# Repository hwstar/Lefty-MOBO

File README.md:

# Lefty-MOBO
Lefty Double Conversion Transceiver Motherboard

This is an HF Motherboard consisting of the entire signal chain from RF in to Speaker, and from Microphone to RF out.  A double conversion topology was chosen to allow the motherboard to operate on all HF bands with minimal intermodulation products close to the operating frequency.

The design uses 5 AS169-73 Skyworks RF switches,  3 Mini Circuits ADE-1 mixers, a pair 45.1 MHz matched Golledge 15 KHz BW IF filters, 6 matched 12.288 MHz crystals for the second IF SSB filter, and 3 2SC3357 low noise RF transistors in the 45.1 MHz "transverter" section. The speaker amplifier is an LM380.

This design was inspired from W7ZOI's single conversion "Lichen" Transceiver originally published in EMRFD. I use the dual JFET IF amplifer, AGC circuit, 3 transistor post-detector audio amplifier, and TX speech amplifier from that design in this design.

Please note that this is not a complete Transceiver system. The transceiver board will additionally require a 3 output VFO (My implementation uses one SI5351, and may use 2 of them in the future so that I can drive all the Mixers at 8mA) ,  external bandpass filter bank, an RF power amplifier, and a TX low pass filter bank.

Mixer 1 (U801) serves as a downconverter in RX mode, and a balanced modulator TX mode. This converts the 45.1 MHz first IF to 12.288 MHz second IF. In TX mode, the VFO provides the carrier frequency (which depends on the characteristics of the crystal filter)

Mixer 2 (U1301) serves as the product detector in RX mode, and a 12.288 MHz upconverter in TX mode.

Mixer 3 (U2201) provides downconversion from the 45.1 MHz first IF to the desired HF band.

Mixer 1, The first IF amplifier, and Mixer 2 operate in the same direction for both TX and RX, but the mixers change function depending upon whether they're being used in TX or RX. A pair of AS169-73 RF switches, some RF chokes and RF traps are used to select the TX mode, and to filter out RF from getting into the audio stages.

The 45.1 MHz first IF uses the "BITx" concept with 2SC3357 bidirectional amplifiers i.e. left-to-right, and right-to-left controlled by a pair of AS169-73 RF switches, and the P13V8_RX and P13V8_TX power rails. The 2SC3357's are biased for 40mA operation.

After Mixer3 there is a stage of TX RF amplification using a 2SC3357 to bring up the signal level what is required for the RF power amplifier (not included on this board). This amplifier is bypassed in RX mode using a AS169-73.

All control to the Lefty Motherboard is done over I2C using an NXP PCA9554 at 7 bit address 0x38. This allows the wiring from the Motherboard to be minimal. 
The I2C interface allows control AS169-73 RF switches, PTT, Rx Audio Mute circuit, AGC on/off, and the TX tune audio oscillator. The SCL and SDA pins at the connector operate at 3.3V and are intended to be used with newer 3.3V microcontrollers available such as the STM32 "black pill".

There is an I2C EEPROM on the board to facilitate storing the TX gain values for each band, and crystal filter 6dB points and bandwidth, and a DAC which is used to control the 12.288 MHz IF amplifier's gain in TX to help flatten out the TX power across all bands. TX gain may also be set manually by removing the DAC and and installing a 20K pot at R918. 

The PCB design was done with KiCAD 5.0. The BOM files are in .csv format and are included in the top level directory. There is a combined BOM, separate top and bottom SMT BOM's, and a PTH BOM.

The gerber files are in the directory TRX_MB_C2_X1

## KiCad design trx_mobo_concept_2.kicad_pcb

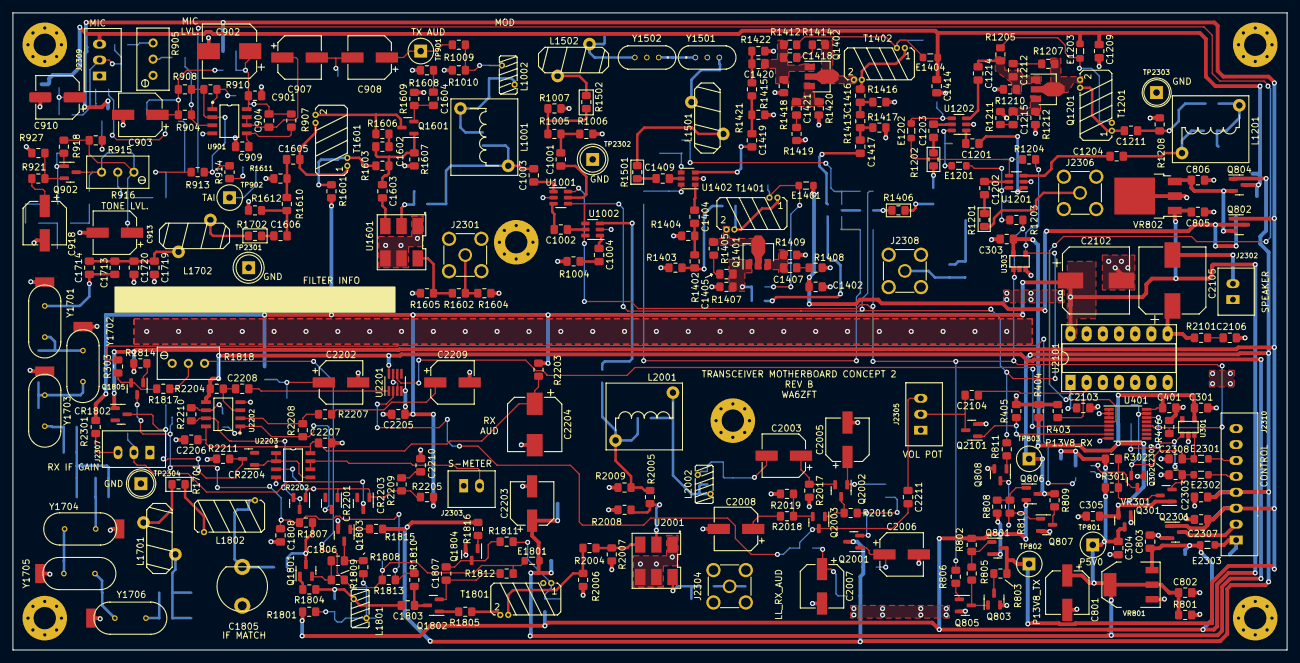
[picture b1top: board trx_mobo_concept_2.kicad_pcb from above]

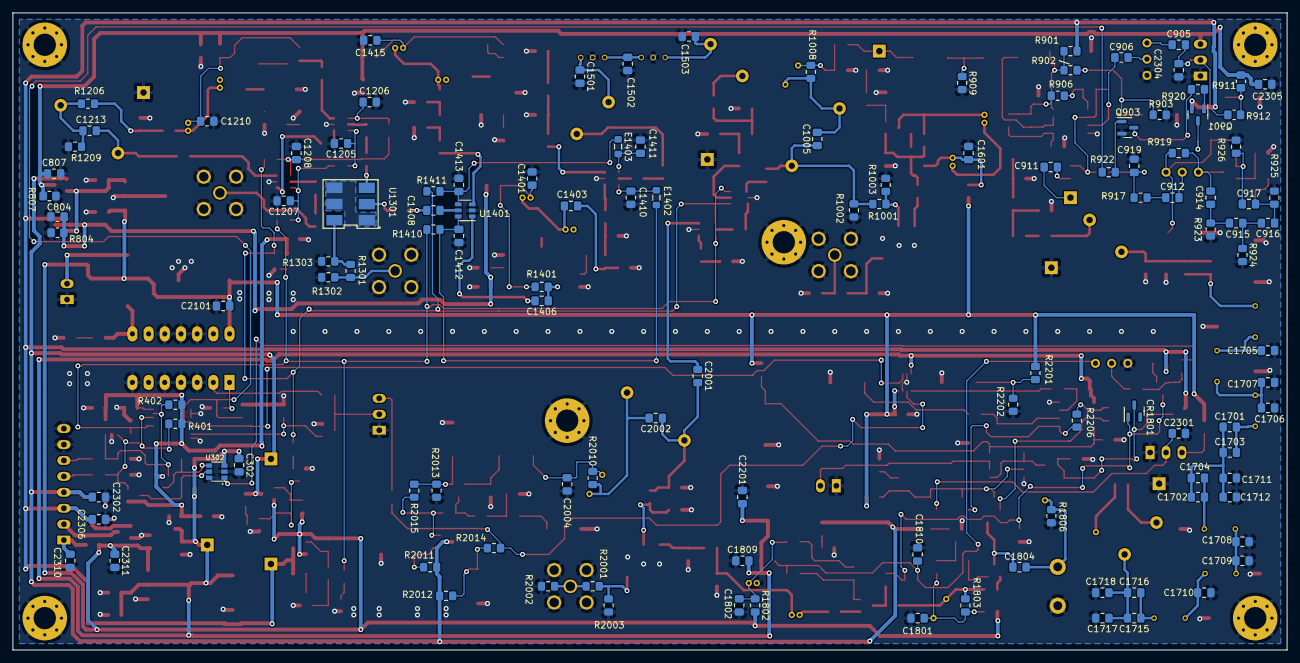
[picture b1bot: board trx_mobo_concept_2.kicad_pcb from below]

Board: 2 copper layers, 200.0 x 100.0 mm, 422 parts (119 on the bottom side), 226 nets.

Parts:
C301, C302, C303, C401, C802, C804, C807, C901, C905, C906, C911, C912, C1004, C1201, C1202, C1203, C1204, C1209, C1210, C1211, C1212, C1214, C1215, C1601, C1602, C1603, C1604, C1605, C1606, C1801, C1802, C1806, C1807, C1808, C1809, C1810, C2004, C2101, C2106, C2201, C2205, C2206, C2207, C2208, C2301, C2302, C2305, C2306, C2310, C2311: 0.1u; C_0805_2012Metric_Pad1.18x1.45mm_HandSolder
C304, C2210: 1u; C_0805_2012Metric_Pad1.18x1.45mm_HandSolder
C305, C2303, C2307: 10u; C_0805_2012Metric_Pad1.18x1.45mm_HandSolder
C801, C903, C907, C908, C910, C913, C918, C2003, C2005, C2006, C2007, C2008, C2202, C2203, C2209: 22u; CP_Elec_6.3x5.7
C803, C805, C806, C2103, C2104, C2211: 4.7u; C_0805_2012Metric_Pad1.18x1.45mm_HandSolder
C902, C2204: 100u; CP_Elec_8x10
C904, C919, C1001, C1002, C1401, C1402, C1403, C1404, C1405, C1406, C1407, C1408, C1409, C1414, C1415, C1416, C1417, C1418, C1419, C1420, C1421, C1803, C1804: 0.01u; C_0805_2012Metric_Pad1.18x1.45mm_HandSolder
C909, C914, C915, C916, C917: 0.0027u; C_0805_2012Metric_Pad1.18x1.45mm_HandSolder
C1003, C1205, C1206, C1207, C1208, C1410, C1411, C1412, C1413, C2001, C2304: 1000p; C_0805_2012Metric_Pad1.18x1.45mm_HandSolder
C1005, C1213, C1706, C1712, C1713, C1717, C1719, C2002: 150p; C_0805_2012Metric_Pad1.18x1.45mm_HandSolder
C1501, C1503: 16p; C_0805_2012Metric_Pad1.18x1.45mm_HandSolder
C1502: 13p; C_0805_2012Metric_Pad1.18x1.45mm_HandSolder
C1701, C1702: 430p; C_0805_2012Metric_Pad1.18x1.45mm_HandSolder
C1703, C1704: 15p; C_0805_2012Metric_Pad1.18x1.45mm_HandSolder
C1705, C1710: 120p; C_0805_2012Metric_Pad1.18x1.45mm_HandSolder
C1707, C1708, C1714, C1715: 10p; C_0805_2012Metric_Pad1.18x1.45mm_HandSolder
C1709, C1716: 150P; C_0805_2012Metric_Pad1.18x1.45mm_HandSolder
C1711: 18p; C_0805_2012Metric_Pad1.18x1.45mm_HandSolder
C1718, C1720: 20p; C_0805_2012Metric_Pad1.18x1.45mm_HandSolder
C1805: 60p; Cap_Trimmer_THT_6mm_plastic
C2102, C2105: 470u; CP_Elec_10x10
C2308, C2309: 100p; C_0805_2012Metric_Pad1.18x1.45mm_HandSolder
CR1801, CR1802, CR2201, CR2202, CR2203, CR2204: BAT54; SOT23-3-SAR-V2
E1201, E1202, E1203, E1401, E1402, E1403, E1404, E1801, E2301, E2302, E2303: FB0805; L_0805_2012Metric_Pad1.05x1.20mm_HandSolder
J2301, J2304, J2306, J2308: CONN_SMA_VERT; SMA_Kinghelm_KHSMA-KE8-G_Vertical
J2302, J2303: CONN2; JST_B2B_XH_A
J2305, J2307, J2309: CONN3; JST_B3B_XH_A
J2310: CONN8; JST_B8B_XH_A
L1001, L1201, L2001: 81nH; AIR_CORE_9MMX6.3MM
L1002, L1801: 27uH; IND_Handwound_FT23
L1501, L1502: 0.563uH; TOROID_T37_VERT
L1701, L1702: 0.97uH; TOROID_T37_VERT
L1802: 4.13uH; IND_Handwound_FT37
L2002: 15uH; IND_Handwound_FT23
MH2301, MH2302, MH2303, MH2304, MH2305, MH2306: MountingHole_Pad; MountingHole_3.5mm_Pad_Via
Q301, Q302, Q803, Q807, Q1805, Q2101, Q2301: BSS138; SOT-23
Q801, Q802, Q804, Q806: SI2369; SOT-23
Q805, Q808, Q902, Q903, Q1601, Q1803, Q1804, Q2001, Q2002, Q2003: MMBT3904; SOT23-3-SAR-V2
Q901: MMBT3906; SOT23-3-SAR-V2
Q1201, Q1401, Q1402: 2SC3357; SOT-89-3
Q1801, Q1802: MMBFJ310; SOT23-3-SAR-V2
R301, R302, R401, R402, R802, R806, R808, R811, R902, R903, R904, R906, R907, R927, R1815, R1816, R2015, R2201, R2202, R2206, R2207, R2210, R2211, R2301: 10K; R_0805_2012Metric_Pad1.15x1.40mm_HandSolder
R303, R805, R810, R901, R921, R2018, R2203: 100; R_0805_2012Metric_Pad1.15x1.40mm_HandSolder
R403, R404, R405, R406, R915, R1009, R2012, R2014, R2209: 1K; R_0805_2012Metric_Pad1.15x1.40mm_HandSolder
R801: 470; R_0805_2012Metric_Pad1.15x1.40mm_HandSolder
R803, R809, R1211, R1601: 10; R_0805_2012Metric_Pad1.15x1.40mm_HandSolder
R804, R807: 10K; R_0805_2012Metric_Pad1.20x1.40mm_HandSolder
R905, R916, R1818: 20K; Potentiometer_Bourns_3296W_Vertical_Screw_SS
R908: 680; R_0805_2012Metric_Pad1.15x1.40mm_HandSolder
R909: 2K; R_0805_2012Metric_Pad1.15x1.40mm_HandSolder
R910, R1813, R1814: 270K; R_0805_2012Metric_Pad1.15x1.40mm_HandSolder
R911: 100; R_0805_2012Metric_Pad1.20x1.40mm_HandSolder
R912: 6.8K; R_0805_2012Metric_Pad1.20x1.40mm_HandSolder
R913, R2204, R2208: 100K; R_0805_2012Metric_Pad1.15x1.40mm_HandSolder
R914: 100K; R_0805_2012Metric_Pad1.20x1.40mm_HandSolder
R917, R920, R922, R923, R924, R925, R2011: 47K; R_0805_2012Metric_Pad1.15x1.40mm_HandSolder
R918: 75K; R_0805_2012Metric_Pad1.15x1.40mm_HandSolder
R919: 22K; R_0805_2012Metric_Pad1.15x1.40mm_HandSolder
R926, R1807, R1808, R1810, R1811: 39K; R_0805_2012Metric_Pad1.15x1.40mm_HandSolder
R1001, R1005, R1201, R1202, R1406, R1501, R1502, R1701, R1702, R1817: 0; R_0805_2012Metric_Pad1.15x1.40mm_HandSolder
R1002, R1003, R1006, R1007: DNI; R_0805_2012Metric_Pad1.15x1.40mm_HandSolder
R1004, R1010: 51; R_0805_2012Metric_Pad1.15x1.40mm_HandSolder
R1008, R1803, R1806, R2010: 2.2K; R_0805_2012Metric_Pad1.15x1.40mm_HandSolder
R1203, R1204, R1410, R1411: 33; R_0805_2012Metric_Pad1.15x1.40mm_HandSolder
R1205, R1401, R1412: 1.1K; R_0805_2012Metric_Pad1.15x1.40mm_HandSolder
R1206, R1402, R1413, R1415, R1610, R2005: 36; R_0805_2012Metric_Pad1.15x1.40mm_HandSolder
R1207: 910; R_0805_2012Metric_Pad1.15x1.40mm_HandSolder
R1208, R1209, R1403, R1404, R1416, R1417, R1421, R1422, R1611, R1612, R2008, R2009: 150; R_0805_2012Metric_Pad1.15x1.40mm_HandSolder
R1210, R1407, R1418: 360; R_0805_2012Metric_Pad1.15x1.40mm_HandSolder
R1212, R1409, R1420: 30; R_0805_2012Metric_Pad1.15x1.40mm_HandSolder
R1301, R1602, R2001, R2004: 18; R_0805_2012Metric_Pad1.15x1.40mm_HandSolder
R1302, R1303, R1604, R1605, R2002, R2003, R2006, R2007: 300; R_0805_2012Metric_Pad1.15x1.40mm_HandSolder
R1405, R1414, R1606: 1.6K; R_0805_2012Metric_Pad1.15x1.40mm_HandSolder
R1408, R1419, R1608: 6.8; R_0805_2012Metric_Pad1.15x1.40mm_HandSolder
R1603: 8.2K; R_0805_2012Metric_Pad1.15x1.40mm_HandSolder
R1607: 1.5K; R_0805_2012Metric_Pad1.15x1.40mm_HandSolder
R1609: 120; R_0805_2012Metric_Pad1.15x1.40mm_HandSolder
R1801, R1802, R1804, R1805: 82; R_0805_2012Metric_Pad1.15x1.40mm_HandSolder
R1809, R1812: 390; R_0805_2012Metric_Pad1.15x1.40mm_HandSolder
R2013, R2017: 3.3K; R_0805_2012Metric_Pad1.15x1.40mm_HandSolder
R2016: 6.8K; R_0805_2012Metric_Pad1.15x1.40mm_HandSolder
R2019: 4.7K; R_0805_2012Metric_Pad1.15x1.40mm_HandSolder
R2101: 2.7; R_0805_2012Metric_Pad1.15x1.40mm_HandSolder
R2205: 2.2M; R_0805_2012Metric_Pad1.15x1.40mm_HandSolder
T1201, T1401, T1402, T1601: XFMR_RF_BIFILAR; XFMR_Handwound_FT37
T1801: FT37-43; XFMR_Handwound_FT37
TP801, TP802, TP803, TP901, TP902, TP2301, TP2302, TP2303, TP2304: TESTPINTPSQ025; TESTPIN
U301: 24CW640; SOT23-5-SAR
U302: MCP4725; SOT23-6-SAR
U303: 74LVC1G00; SOT23-5-SAR
U401: PCA9554APW; TSSOP-16_4.4x5mm_P0.65mm
U901, U2202, U2203: LMC6482; SOIC8N-SAR
U1001, U1002, U1201, U1202, U1401, U1402: AS169-73; SOT-23-6
U1301, U1601, U2001: ADE-1; MCL-6-SMD_7R97X5R59
U2101: LM380N; DIP-14_W7.62mm_Socket_LongPads
U2201: DG449DS-T1-E3; SOT-23-8_Handsoldering
VR301: ME6211A33M3G-N; SOT23-3-SAR-V2
VR801: NCP1117-5.0_SOT223; SOT-223-TAB-2-SAR
VR802: MC78M08CDTRKG; TO-252-3_TabPin2
Y1501, Y1502: 45.1 MHz; MCF-1.875_7.8x3.2
Y1701, Y1702, Y1703, Y1704, Y1705, Y1706: 12.288 MHz; Crystal_HC49_Vertical_With_Grounding_Pad

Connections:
/top/DIS_AGC_3V3: R404.1, U401.5 (IO1), U2201.6 (IN)
/top/ENA_TUNE_OSC_3V3: R403.1, R922.2, U401.4 (IO0)
/top/IF_GAIN_WIPER: C2301.1, CR2203.3 (C), J2307.2
/top/LO_FIRST: J2301.1, R1602.2, R1604.1
/top/LO_SECOND: J2304.1, R2001.2, R2002.1
/top/P5V0: C302.1, C304.1, C801.1, C802.1, C1809.1, C2201.1, C2203.1, E1801.1, R301.1, R302.1, R801.1, R2204.1, TP801.1 (TP), U302.3 (VDD), U2201.8, U2202.5 (+), VR301.3 (IN), VR801.2 (OUT)
/top/P13V8: C803.1, C805.1, C2101.1, C2102.1, C2205.1, C2311.1, E2303.2, Q801.2 (S), Q806.2 (S), R802.1, R808.1, R1601.2, R1801.2, R1802.2, R2201.2, R2203.2, R2205.2, R2301.1, U2101.14, U2201.4 (V+), VR801.3 (IN), VR802.1 (IN)
/top/P13V8_RX: C2302.1, C2303.1, J2310.4, Q804.1 (G), Q806.3 (D), Q2001.3 (C), R809.1, R1815.2, R1816.2, R2011.1, R2012.1, TP803.1 (TP)
/top/P13V8_TX: C2306.1, C2307.1, CR1802.1 (A), J2310.3, Q801.3 (D), Q802.1 (G), Q901.2 (E), Q2301.1 (G), R803.1, R901.2, R1814.1, TP802.1 (TP)
/top/PTT_3V3: R406.1, R806.2, R1203.2, R1410.2, U303.1, U303.2, U401.12 (IO7), U1001.6 (V2), U1002.6 (V2)
/top/PTT_3V3_N: R811.2, R1204.2, R1411.2, U303.4, U1001.4 (V1), U1002.4 (V1)
/top/RX_AUDIO_SPEAKER: C2105.2, J2302.2
/top/RX_AUDIO_TOP: C2211.1, J2305.3
/top/RX_AUDIO_WIPER: C2104.2, J2305.2, Q2101.3 (D)
/top/SCL_I2C_3V3: C2309.1, E2302.2, Q301.2 (S), R401.2, U301.1 (SCL), U401.14 (SCL)
/top/SDA_I2C_3V3: C2308.1, E2301.2, Q302.2 (S), R402.2, U301.3 (SDA), U401.15 (SDA)
/top/S_METER: J2303.2, U2203.6 (-), U2203.7
/top/TRX_RF: J2306.1, R1201.2
/top/TX_AUDIO_IN: C905.2, C2304.1, J2309.2, R912.1
/top/connectors/LO_THIRD: J2308.1, R1301.2, R1302.1
/top/connectors/P8V0_TX: C807.1, C1209.1, C1414.1, C2305.1, E1203.1, E1404.1, J2309.3, Q804.3 (D), R807.1, R911.2
/top/connectors/SCL_I2C_CONN_3V3: E2302.1, J2310.5
/top/connectors/SDA_I2C_CONN_3V3: E2301.1, J2310.6
/top/connectors/~TX: J2310.2, Q2301.3 (D)
/top/i2c/SCL_I2C_5V0: Q301.3 (D), R301.2, U302.5 (SCL)
/top/i2c/SDA_I2C_5V0: Q302.3 (D), R302.2, U302.4 (SDA)
/top/i2c/TX_IF_GAIN: Q1805.2 (S), R303.1, R1817.2
/top/radio/MUTE_RX_AUDIO: Q2101.1 (G), R405.1, U401.7 (IO3)
/top/radio/ifagc/AGC_IN: CR1801.3 (C), CR1802.3 (C), CR2204.3 (C), R2211.2
/top/radio/ifagc/C903_RF: C1803.1, Q1802.3 (G), R1810.1
/top/radio/ifagc/C904_RF: C1804.1, Q1801.3 (G), R1807.1
/top/radio/ifagc/IF_IN: L1802.2, R1701.2
/top/radio/ifagc/IF_OUT: R2004.2, R2006.1, T1801.4 (S2)
/top/radio/ifagc/L902_RF: C1804.2, C1805.1, L1802.1, R1806.1
/top/radio/ifagc/Q901_RF: Q1801.1 (D), R1804.2
/top/radio/ifagc/Q902_RF: Q1802.1 (D), R1805.2
/top/radio/ifagc/R904_RF: C1803.2, L1801.2, R1803.2, R1804.1
/top/radio/ifagc/R905_RF: R1805.1, T1801.2 (PR2)
/top/radio/mixamp/C805_RF: C1605.1, R1610.2, R1611.1
/top/radio/mixamp/C806_RF: C1606.2, R1610.1, R1612.1
/top/radio/mixamp/IF_OUT_12R288: C1606.1, R1702.1
/top/radio/mixamp/Q801_B_RF: C1602.2, C1603.1, Q1601.1 (B), R1603.2, R1607.1
/top/radio/mixamp/Q810_C_RF: Q1601.3 (C), R1606.1, T1601.2 (PR2)
/top/radio/mixamp/R801_PWR: C1601.1, R1601.1, R1603.1, T1601.3 (S1)
/top/radio/mixamp/RX_IF_IN_45R1: R1001.1, R1003.1, U1601.2 (IF)
/top/radio/mixamp/T801_RF: C1605.2, T1601.1 (PR1), T1601.4 (S2)
/top/radio/mixamp/U801_LO: R1602.1, R1605.1, U1601.6 (LO)
/top/radio/mixamp/U801_RF: C1603.2, U1601.3 (RF)
/top/radio/prod_det_tx_mix/TX_IF_OUT_45R1: C2001.1, U1002.3
/top/radio/prod_det_tx_mix/agc/APBIAS: C2202.1, R2201.1, R2202.2
/top/radio/prod_det_tx_mix/agc/LL_RX_AUDIO: C2211.2, Q2003.3 (C), R2014.2, U2201.2
/top/radio/prod_det_tx_mix/second_mixer_audio_preamp/L1301_RF: C2002.2, L2001.2, L2002.2, R2010.1
/top/radio/prod_det_tx_mix/second_mixer_audio_preamp/R1301_RF: R2001.1, R2003.1, U2001.6 (LO)
/top/radio/prod_det_tx_mix/second_mixer_audio_preamp/R1304_RF: R2004.1, R2007.1, U2001.3 (RF)
/top/radio/prod_det_tx_mix/second_mixer_audio_preamp/R1305_RF: C2001.2, C2002.1, L2001.1, R2005.1, R2009.1
/top/radio/prod_det_tx_mix/second_mixer_audio_preamp/U1301_RF: R2005.2, R2008.1, U2001.2 (IF)
/top/radio/rf_45r1_mic_amp_tune_osc/if_45r1_mic_amp_tune_osc/P8V0_RX: C804.1, C1402.1, E1401.1, Q802.3 (D), R804.1
/top/radio/rf_45r1_mic_amp_tune_osc/if_45r1_mic_amp_tune_osc/TRX_IF_45R1: R1005.1, R1007.1, R1502.1
/top/radio/rf_45r1_mic_amp_tune_osc/if_45r1_mic_amp_tune_osc/speech_amp/AUDIO_O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: C908.1, R1009.2, TP901.1 (TP)
/top/radio/rf_45r1_mic_amp_tune_osc/if_45r1_mic_amp_tune_osc/trx_switch/C1802_RF: C1001.2, R1005.2, R1006.1
/top/radio/rf_45r1_mic_amp_tune_osc/if_45r1_mic_amp_tune_osc/trx_switch/C1805_RF: C1003.2, C1005.1, L1001.1, R1001.2, R1002.1
/top/radio/rf_45r1_mic_amp_tune_osc/if_45r1_mic_amp_tune_osc/trx_switch/L1802_RF: C1005.2, L1001.2, L1002.1, R1008.1
/top/radio/rf_45r1_mic_amp_tune_osc/if_45r1_mic_amp_tune_osc/trx_switch/U1801_C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: C1001.1, U1001.5
/top/radio/rf_45r1_mic_amp_tune_osc/if_45r1_mic_amp_tune_osc/trx_switch/U1801_N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: C1003.1, U1001.1
/top/radio/rf_45r1_mic_amp_tune_osc/if_45r1_mic_amp_tune_osc/trx_switch/U1801_N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: C1002.2, U1001.3
/top/radio/rf_45r1_mic_amp_tune_osc/if_45r1_mic_amp_tune_osc/trx_switch/U1802_C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: C1002.1, U1002.5
/top/radio/rf_45r1_mic_amp_tune_osc/if_45r1_mic_amp_tune_osc/trx_switch/U1802_N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: C1004.1, U1002.1
/top/radio/rf_45r1_mic_amp_tune_osc/transverter/BD_RF_AMP/BDA_RIGHT: R1202.1, U1301.3 (RF)
/top/radio/rf_45r1_mic_amp_tune_osc/transverter/BD_RF_AMP/C2303_RF: C1203.1, R1202.2
/top/radio/rf_45r1_mic_amp_tune_osc/transverter/BD_RF_AMP/C2311_RF: C1211.1, R1206.2, R1208.1
/top/radio/rf_45r1_mic_amp_tune_osc/transverter/BD_RF_AMP/C2314_RF: C1212.2, C1214.1, Q1201.1 (B), R1205.2, R1210.1
/top/radio/rf_45r1_mic_amp_tune_osc/transverter/BD_RF_AMP/L2RRF_IN: C1201.2, U1201.1
/top/radio/rf_45r1_mic_amp_tune_osc/transverter/BD_RF_AMP/L2RRF_IN_C: C1201.1, U1202.1
/top/radio/rf_45r1_mic_amp_tune_osc/transverter/BD_RF_AMP/Q2301_RF: Q1201.2 (C), R1207.1, T1201.2 (PR2)
/top/radio/rf_45r1_mic_amp_tune_osc/transverter/BD_RF_AMP/R2L_RF_IN: C1214.2, U1202.3
/top/radio/rf_45r1_mic_amp_tune_osc/transverter/BD_RF_AMP/R2L_RF_OUT: C1204.1, C1213.2, L1201.2
/top/radio/rf_45r1_mic_amp_tune_osc/transverter/BD_RF_AMP/R2301_RF: C1202.2, R1201.1
/top/radio/rf_45r1_mic_amp_tune_osc/transverter/BD_RF_AMP/R2306_RF: C1213.1, L1201.1, R1206.1, R1209.1
/top/radio/rf_45r1_mic_amp_tune_osc/transverter/BD_RF_AMP/T2301_RF: C1211.2, T1201.1 (PR1), T1201.4 (S2)
/top/radio/rf_45r1_mic_amp_tune_osc/transverter/BD_RF_AMP/U2301_C_RF: C1202.1, U1201.5
/top/radio/rf_45r1_mic_amp_tune_osc/transverter/BD_RF_AMP/U2302_C_RF: C1203.2, U1202.5
/top/radio/rf_45r1_mic_amp_tune_osc/transverter/THIRD_MIXER/IF: R1406.2, U1301.2 (IF)
/top/radio/rf_45r1_mic_amp_tune_osc/transverter/THIRD_MIXER/R2201_RF: R1301.1, R1303.1, U1301.6 (LO)
/top/radio/rf_45r1_mic_amp_tune_osc/transverter/bd_amp_45R1/BDA_RIGHT: C1409.1, R1501.2
/top/radio/rf_45r1_mic_amp_tune_osc/transverter/bd_amp_45R1/C2103_RF: C1403.1, R1402.2, R1403.1
/top/radio/rf_45r1_mic_amp_tune_osc/transverter/bd_amp_45R1/C2104_RF: C1404.1, U1402.1
/top/radio/rf_45r1_mic_amp_tune_osc/transverter/bd_amp_45R1/C2106_RF: C1405.2, C1406.1, Q1401.1 (B), R1401.2, R1407.1
/top/radio/rf_45r1_mic_amp_tune_osc/transverter/bd_amp_45R1/C2108_RF: C1408.1, U1401.5
/top/radio/rf_45r1_mic_amp_tune_osc/transverter/bd_amp_45R1/C2116_RF: C1416.1, R1413.2, R1416.1
/top/radio/rf_45r1_mic_amp_tune_osc/transverter/bd_amp_45R1/C2119_RF: C1419.1, R1415.2, R1421.1
/top/radio/rf_45r1_mic_amp_tune_osc/transverter/bd_amp_45R1/C2120_RF: C1418.2, C1420.1, Q1402.1 (B), R1412.2, R1418.1
/top/radio/rf_45r1_mic_amp_tune_osc/transverter/bd_amp_45R1/L2RRF_IN: C1406.2, U1401.1
/top/radio/rf_45r1_mic_amp_tune_osc/transverter/bd_amp_45R1/Q2101_RF: Q1401.2 (C), R1405.1, T1401.2 (PR2)
/top/radio/rf_45r1_mic_amp_tune_osc/transverter/bd_amp_45R1/Q2102_RF: Q1402.2 (C), R1414.1, T1402.2 (PR2)
/top/radio/rf_45r1_mic_amp_tune_osc/transverter/bd_amp_45R1/R2L_RF_IN: C1419.2, U1402.3
/top/radio/rf_45r1_mic_amp_tune_osc/transverter/bd_amp_45R1/R2L_RF_OUT: C1417.1, U1401.3
/top/radio/rf_45r1_mic_amp_tune_osc/transverter/bd_amp_45R1/R2102_RF: C1404.2, R1402.1, R1404.1
/top/radio/rf_45r1_mic_amp_tune_osc/transverter/bd_amp_45R1/R2106_RF: C1408.2, R1406.1
/top/radio/rf_45r1_mic_amp_tune_osc/transverter/bd_amp_45R1/R2114_RF: C1417.2, R1413.1, R1417.1
/top/radio/rf_45r1_mic_amp_tune_osc/transverter/bd_amp_45R1/R2118_RF: C1420.2, R1415.1, R1422.1
/top/radio/rf_45r1_mic_amp_tune_osc/transverter/bd_amp_45R1/T2101_RF: C1403.2, T1401.1 (PR1), T1401.4 (S2)
/top/radio/rf_45r1_mic_amp_tune_osc/transverter/bd_amp_45R1/T2102_RF: C1416.2, T1402.1 (PR1), T1402.4 (S2)
/top/radio/rf_45r1_mic_amp_tune_osc/transverter/bd_amp_45R1/U2102_RF: C1409.2, U1402.5
/top/radio/rf_45r1_mic_amp_tune_osc/transverter/roofing_filter/L2001_RF: C1501.1, L1501.2, Y1501.1
/top/radio/rf_45r1_mic_amp_tune_osc/transverter/roofing_filter/L2002_RF: L1502.2, R1502.2
/top/radio/rf_45r1_mic_amp_tune_osc/transverter/roofing_filter/R2001_RF: L1501.1, R1501.1
/top/radio/rf_45r1_mic_amp_tune_osc/transverter/roofing_filter/Y2001_RF: C1502.1, Y1501.3, Y1502.3
/top/radio/rf_45r1_mic_amp_tune_osc/transverter/roofing_filter/Y2002_RF: C1503.1, L1502.1, Y1502.1
/top/radio/xtal_filter/C701_RF: C1701.1, C1702.2, C1703.1, C1704.2, C1711.1, C1712.1
/top/radio/xtal_filter/C702_RF: C1702.1, C1704.1, Y1704.1
/top/radio/xtal_filter/C713_RF: C1713.1, C1714.1, Y1701.1
/top/radio/xtal_filter/C715_RF: C1715.2, C1716.2, C1717.1, C1718.1, L1701.2
/top/radio/xtal_filter/C719_RF: C1713.2, C1714.2, C1719.1, C1720.1, L1702.1
/top/radio/xtal_filter/L701_RF: L1701.1, R1701.1
/top/radio/xtal_filter/R702_RF: L1702.2, R1702.2
/top/radio/xtal_filter/Y701_RF: C1705.1, Y1701.3, Y1702.1
/top/radio/xtal_filter/Y702_RF: C1706.1, C1707.1, Y1702.3, Y1703.1
/top/radio/xtal_filter/Y703_RF: C1701.2, C1703.2, Y1703.3
/top/radio/xtal_filter/Y704_RF: C1708.1, C1709.1, Y1704.3, Y1705.1
/top/radio/xtal_filter/Y705_RF: C1710.1, Y1705.3, Y1706.1
/top/radio/xtal_filter/Y706_RF: C1715.1, C1716.1, Y1706.3
GND: C301.2, C302.2, C303.2, C304.2, C305.2, C401.2, C801.2, C802.2, C803.2, C804.2, C805.2, C806.2, C807.2, C901.2, C902.2, C903.2, C909.2, C910.2, C913.2, C918.2, C919.2, C1205.2, C1206.2, C1207.2, C1208.2, C1209.2, C1210.2, C1401.2, C1402.2, C1410.2, C1411.2, C1412.2, C1413.2, C1414.2, C1415.2, C1501.2, C1502.2, C1503.2, C1601.2, C1705.2, C1706.2, C1707.2, C1708.2, C1709.2, C1710.2, C1711.2, C1712.2, C1717.2, C1718.2, C1719.2, C1720.2, C1801.2, C1802.2, C1805.2, C1808.2, C1809.2, C1810.2, C2004.2, C2005.2, C2006.2, C2007.2, C2008.2, C2101.2, C2102.2, C2103.2, C2106.2, C2201.2, C2202.2, C2203.2, C2204.2, C2205.2, C2206.2, C2207.2, C2209.2, C2210.2, C2301.2, C2302.2, C2303.2, C2304.2, C2305.2, C2306.2, C2307.2, C2308.2, C2309.2, C2310.2, C2311.2, J2301.2, J2301.3, J2301.4, J2301.5, J2302.1, J2303.1, J2304.2, J2304.3, J2304.4, J2304.5, J2305.1, J2306.2, J2306.3, J2306.4, J2306.5, J2307.1, J2308.2, J2308.3, J2308.4, J2308.5, J2309.1, J2310.7, J2310.8, MH2301.1, MH2302.1, MH2303.1, MH2304.1, MH2305.1, MH2306.1, Q803.2 (S), Q805.2 (E), Q807.2 (S), Q808.2 (E), Q903.2 (E), Q1803.2 (E), Q1804.2 (E), Q2101.2 (S), Q2301.2 (S), R403.2, R404.2, R405.2, R406.2, R801.2, R804.2, R807.2, R903.2, R905.1, R909.2, R923.2, R924.2, R925.2, R926.2, R927.2, R1002.2, R1003.2, R1004.2, R1006.2, R1007.2, R1010.2, R1208.2, R1209.2, R1210.2, R1211.2, R1212.2, R1302.2, R1303.2, R1403.2, R1404.2, R1407.2, R1408.2, R1409.2, R1416.2, R1417.2, R1418.2, R1419.2, R1420.2, R1421.2, R1422.2, R1604.2, R1605.2, R1607.2, R1608.2, R1609.2, R1611.2, R1612.2, R1806.2, R1818.1, R2002.2, R2003.2, R2006.2, R2007.2, R2008.2, R2009.2, R2013.1, R2017.2, R2019.2, R2202.1, R2211.1, T1801.3 (S1), TP2301.1 (TP), TP2302.1 (TP), TP2303.1 (TP), TP2304.1 (TP), U301.2 (VSS), U302.2 (VSS), U302.6 (A0), U303.3, U401.1 (A0), U401.2 (A1), U401.3 (A2), U401.8 (VSS), U901.4 (V-), U1001.2 (GND), U1002.2 (GND), U1201.2 (GND), U1202.2 (GND), U1301.1 (GND), U1301.4, U1301.5 (GND), U1401.2 (GND), U1402.2 (GND), U1601.1 (GND), U1601.4, U1601.5 (GND), U2001.1 (GND), U2001.4, U2001.5 (GND), U2101.3, U2101.4, U2101.5, U2101.7, U2101.10, U2101.11, U2101.12, U2201.3 (GND), U2201.7 (V-), U2202.4 (V-), U2203.4 (V-), VR301.1 (GND), VR801.1 (GND), VR802.2 (GND), Y1501.2, Y1502.2, Y1701.2, Y1702.2, Y1703.2, Y1704.2, Y1705.2, Y1706.2
unnamed: C806.1, Q802.2 (S), Q804.2 (S), VR802.3 (OUT)
unnamed: C901.1, C902.1, R901.1, R902.1, U901.8 (V+)
unnamed: C903.1, R902.2, R903.1, R904.2, R908.2
unnamed: C904.1, C907.1, U901.6 (-), U901.7
unnamed: C904.2, R906.1, R907.2
unnamed: C905.1, R905.3
unnamed: C906.1, R904.1, U901.3 (+)
unnamed: C906.2, R905.2
unnamed: C907.2, C908.2, R909.1
unnamed: C909.1, R907.1, U901.5 (+)
unnamed: C910.1, R911.1, R912.2
unnamed: C911.1, R914.1
unnamed: C911.2, TP902.1 (TP)
unnamed: C912.1, R917.2
unnamed: C912.2, R916.2
unnamed: C913.1, R915.1, R916.1, R918.1, R919.1
unnamed: C914.1, C915.2, R923.1
unnamed: C914.2, Q902.3 (C), R916.3, R919.2
unnamed: C915.1, C916.2, R924.1
unnamed: C916.1, C917.2, R925.1
unnamed: C917.1, Q902.1 (B), R918.2, R926.1
unnamed: C918.1, R921.1
unnamed: C919.1, R913.2, R917.1
unnamed: C1004.2, R1004.1
unnamed: C1204.2, U1201.3
unnamed: C1205.1, E1201.2, U1202.6 (V2)
unnamed: C1206.1, E1202.2, U1202.4 (V1)
unnamed: C1207.1, E1201.1, R1203.1, U1201.6 (V2)
unnamed: C1208.1, E1202.1, R1204.1, U1201.4 (V1)
unnamed: C1210.1, E1203.2, R1205.1, T1201.3 (S1)
unnamed: C1212.1, R1207.2
unnamed: C1215.1, Q1201.3 (E), R1212.1
unnamed: C1215.2, R1211.1
unnamed: C1401.1, E1401.2, R1401.1, T1401.3 (S1)
unnamed: C1405.1, R1405.2
unnamed: C1407.1, Q1401.3 (E), R1409.1
unnamed: C1407.2, R1408.1
unnamed: C1410.1, E1402.2, U1402.6 (V2)
unnamed: C1411.1, E1403.2, U1402.4 (V1)
unnamed: C1412.1, E1402.1, R1410.1, U1401.6 (V2)
unnamed: C1413.1, E1403.1, R1411.1, U1401.4 (V1)
unnamed: C1415.1, E1404.2, R1412.1, T1402.3 (S1)
unnamed: C1418.1, R1414.2
unnamed: C1421.1, Q1402.3 (E), R1420.1
unnamed: C1421.2, R1419.1
unnamed: C1602.1, R1606.2
unnamed: C1604.1, Q1601.2 (E), R1609.1
unnamed: C1604.2, R1608.1
unnamed: C1801.1, L1801.1, R1801.1, R1803.1, R1808.1
unnamed: C1802.1, R1802.1, R1811.1, T1801.1 (PR1)
unnamed: C1806.1, Q1801.2 (S), R1809.1
unnamed: C1806.2, Q1803.3 (C), R1808.2
unnamed: C1807.1, Q1802.2 (S), R1812.1
unnamed: C1807.2, Q1804.3 (C), R1811.2
unnamed: C1808.1, CR1801.1 (A), Q1805.3 (D), R1807.2, R1810.2, R1813.1
unnamed: C1810.1, E1801.2, R1809.2, R1812.2, R1813.2, R1818.3
unnamed: C2003.1, Q2002.2 (E), R2017.1
unnamed: C2003.2, C2004.1, L2002.1, R2010.2
unnamed: C2005.1, Q2002.1 (B), R2013.2, R2015.2
unnamed: C2006.1, Q2001.1 (B), R2011.2
unnamed: C2007.1, R2012.2, R2014.1
unnamed: C2008.1, R2018.2
unnamed: C2103.1, U2101.1
unnamed: C2104.1, U2101.2 (+)
unnamed: C2105.1, R2101.1, U2101.8
unnamed: C2106.1, R2101.2
unnamed: C2204.1, C2206.1, C2207.1, R2203.1, U2202.8 (V+), U2203.8 (V+)
unnamed: C2208.1, R2204.2, U2202.3 (+)
unnamed: C2208.2, U2201.1
unnamed: C2209.1, R2207.2
unnamed: C2210.1, R2209.2
unnamed: C2310.1, E2303.1, J2310.1
unnamed: CR2201.1 (A), CR2202.1 (A), CR2203.1 (A), R2205.1, R2209.1, U2203.3 (+)
unnamed: CR2201.3 (C), R2206.2, R2208.1, U2202.1
unnamed: CR2202.3 (C), R2210.1, U2202.7
unnamed: CR2204.1 (A), U2203.1, U2203.2 (-), U2203.5 (+)
unnamed: J2307.3, R2301.2
unnamed: L1002.2, R1008.2, R1009.1, R1010.1
unnamed: Q801.1 (G), R802.2, R805.1
unnamed: Q803.1 (G), Q805.3 (C), R805.2
unnamed: Q803.3 (D), R803.2
unnamed: Q805.1 (B), R806.1
unnamed: Q806.1 (G), R808.2, R810.1
unnamed: Q807.1 (G), Q808.3 (C), R810.2
unnamed: Q807.3 (D), R809.2
unnamed: Q808.1 (B), R811.1
unnamed: Q901.1 (B), R920.1
unnamed: Q901.3 (C), R915.2
unnamed: Q902.2 (E), R921.2, R927.1
unnamed: Q903.1 (B), R922.1
unnamed: Q903.3 (C), R920.2
unnamed: Q1803.1 (B), R1815.1
unnamed: Q1804.1 (B), R1816.1
unnamed: Q1805.1 (G), R1814.2
unnamed: Q2001.2 (E), R2015.1, R2016.1
unnamed: Q2002.3 (C), Q2003.1 (B), R2016.2
unnamed: Q2003.2 (E), R2018.1, R2019.1
unnamed: R303.2, U302.1 (VOUT)
unnamed: R906.2, R910.1, U901.1
unnamed: R908.1, R910.2, R913.1, R914.2, U901.2 (-)
unnamed: R1817.1, R1818.2
unnamed: R2206.1, R2210.2, U2202.6 (-)
unnamed: R2207.1, R2208.2, U2202.2 (-)
P3V3: C301.1, C303.1, C305.1, C401.1, Q301.1 (G), Q302.1 (G), R401.1, R402.1, U301.4 (VCC), U303.5, U401.16 (VDD), VR301.2 (OUT)

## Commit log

2022-02-10 Initial files
2022-02-10 Add pic
2022-02-12 Add picture, correct C2002 value in BOM.
2022-02-12 Change TI to NXP
2022-02-19 Update README.md with latest project state
2022-02-23 Change to KiCAD 6
2022-02-23 Update pcb database to version 6
2022-02-24 Sync PCB with schematic
2022-02-27 Fix BOM part number errors and out of sync footprints which happened during conversion from Kicad 5 to 6
2022-02-27 Fix missing part number for 330 ohm resistor
2022-02-27 Fix incorrect part number for 470uf capacitor
2022-02-28 Fix R917 silkscreen
2022-03-10 Change bias resistors on 2SC3357 amplifiers to stay under 12V across Vbe.
2022-05-02 trx_mobo_concept_2_B. Change design to use a dedicated 8V supply for the 2SC3357 parts. Add S-Meter connector. Change mic connector to 3 pins and add 8V sopower supply to pin 3.
2022-05-02 Fix 12.288MHz part number in schematic, regenerate BOM's.
